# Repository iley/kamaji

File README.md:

# Kamaji quiz game system

See [kamaji.cc](http://kamaji.cc) for assembly instructions and additional information.

Directories:

* `firmware`: main source code;
* `demo`: code samples;
* `3d`: [OpenSCAD](http://www.openscad.org/) models for the enclosure;
* `pcb`: schematic and printed circuit board layout in [KiCAD](http://kicad-pcb.org/) format;
* `misc`: the rest.

## SDK

We use [PlatformIO](http://platformio.org) with
[Arduino](http://platformio.org/frameworks/arduino) framework. It should also
be possible to compile the code with the official Arduino IDE.

## Compile and flash firmware

For v1 and v3 custom fuses must be programmed before first flashing.

```
pio run -e v1 -t fuses
```

Select the correct board version (v1, v2, v3) and flash it with:

```
pio run -e v1 -t upload
```

## Hardware

**The recommended version for new builds is "Classic V1".**

* V1 uses an ATmega328p running at 8MHz without an external oscillator. [USBasp](http://www.fischl.de/usbasp/) can be used for programming.
* V2 uses ATmega32u4 and a 128x64 graphics screen.
* V3 runs on ATmega328p with a 16MHz oscillator and and utilizes a PCF8574 I/O extender chip.
* "Classic V1" is an updated revision of V1. Fully compatible from software point of view.
* "Headless" is a USB MIDI device without a screen or buttons. Built around "Pro Micro" boards (ATMega32U4).

## Code style

Let's stick to [Google C++ Style Guide](https://google.github.io/styleguide/cppguide.html).

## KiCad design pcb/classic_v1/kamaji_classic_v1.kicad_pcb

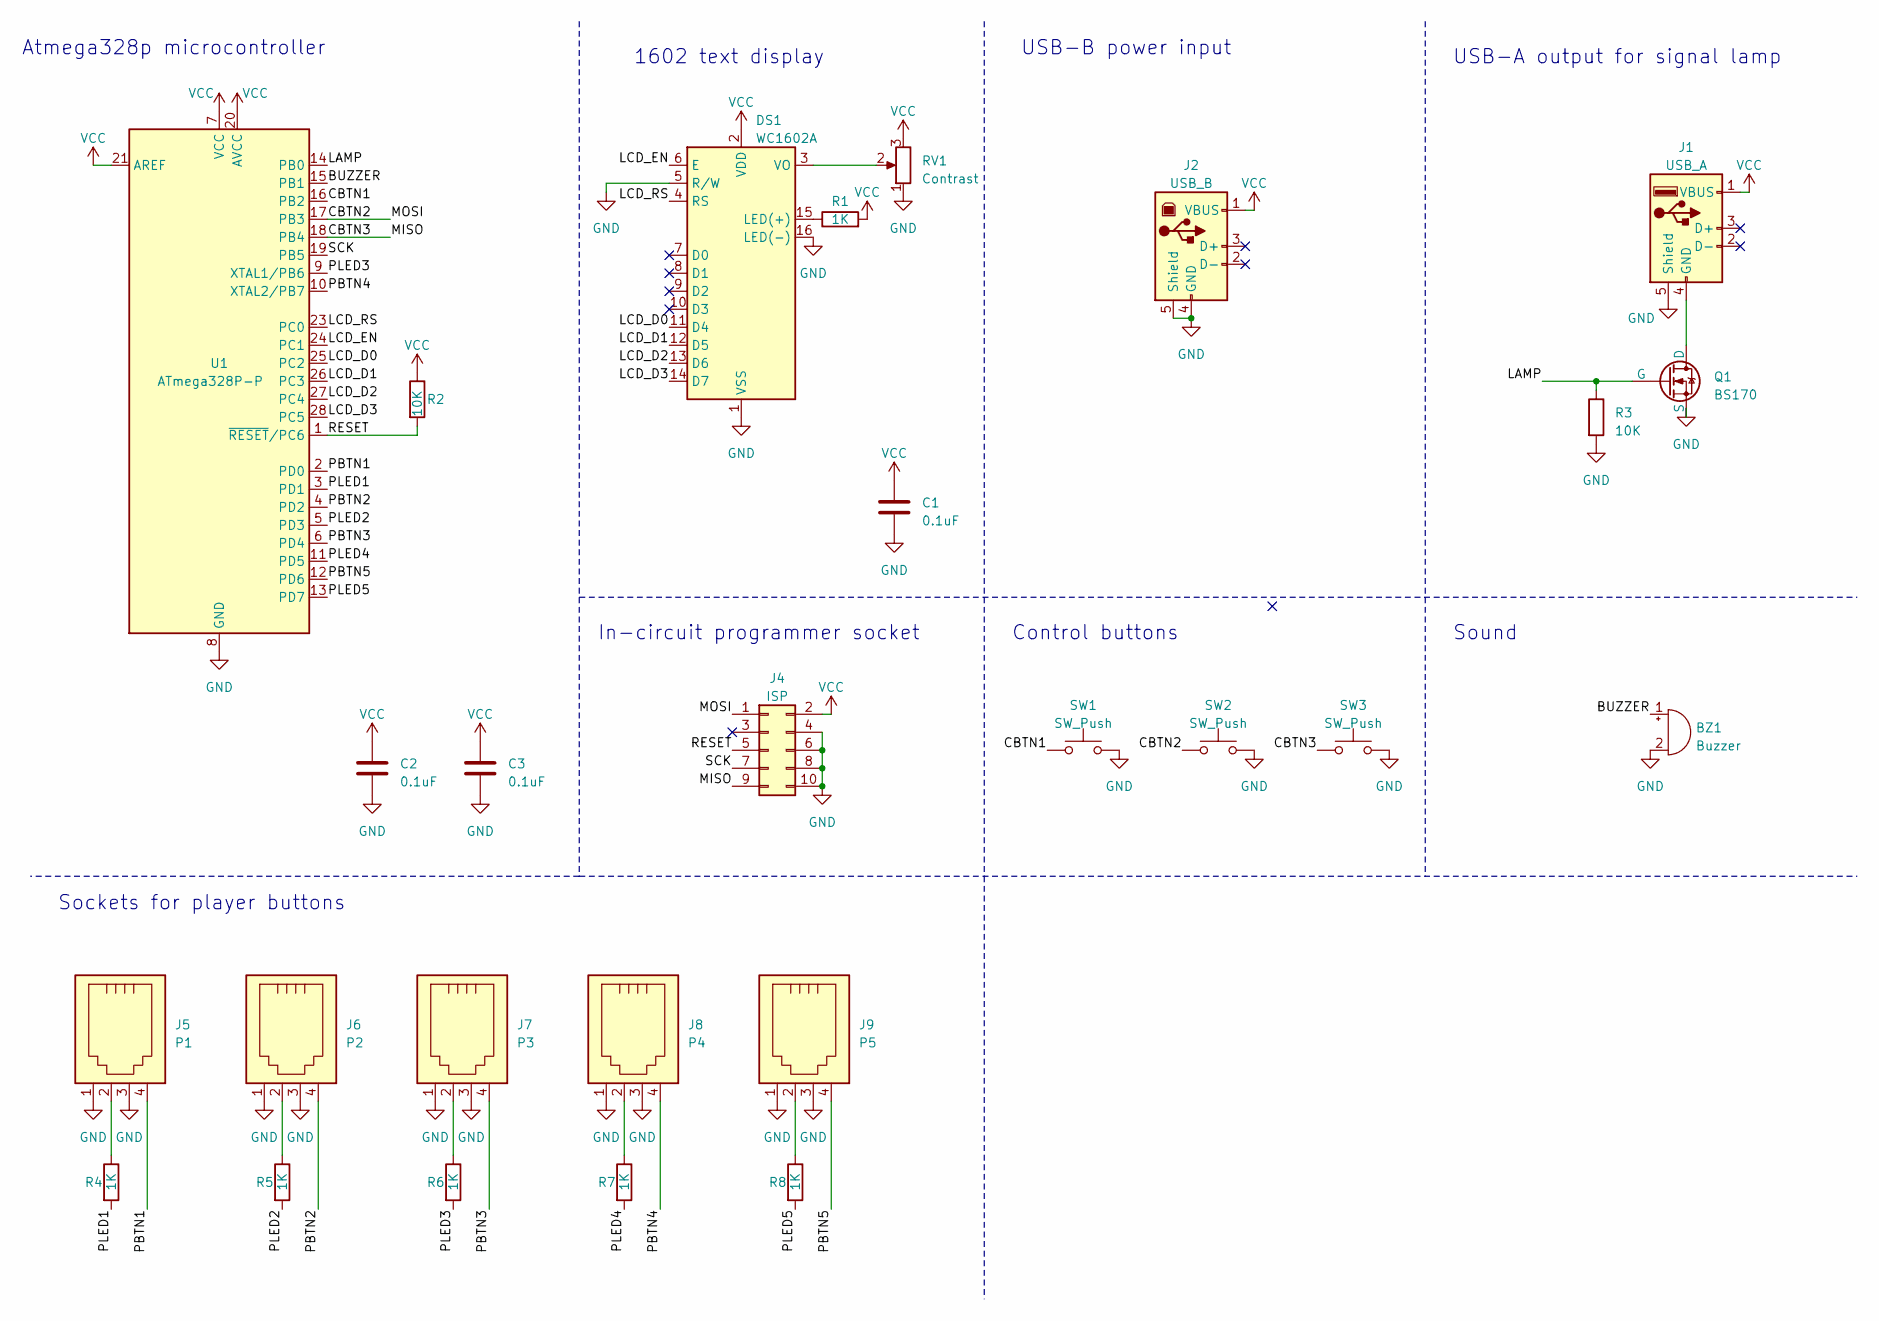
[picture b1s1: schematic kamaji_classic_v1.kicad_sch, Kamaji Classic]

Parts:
BZ1: Buzzer; Buzzer_12x9.5RM7.6
C1, C2, C3: 0.1uF; C_Disc_D3.8mm_W2.6mm_P2.50mm
DS1: WC1602A
J1: USB_A; USB_A_Connfly_DS1095
J2: USB_B; USB_B_Lumberg_2411_02_Horizontal
J4: ISP; IDC-Header_2x05_P2.54mm_Horizontal
J5: P1; RJ10
J6: P2; RJ10
J7: P3; RJ10
J8: P4; RJ10
J9: P5; RJ10
Q1: BS170; TO-92_HandSolder
R1, R4, R5, R6, R7, R8: 1K; R_Axial_DIN0207_L6.3mm_D2.5mm_P10.16mm_Horizontal
R2, R3: 10K; R_Axial_DIN0207_L6.3mm_D2.5mm_P10.16mm_Horizontal
RV1: Contrast; Potentiometer_Vishay_T73YP_Vertical
SW1, SW2, SW3: SW_Push; SW_PUSH-12mm
U1: ATmega328P-P; DIP-28_W7.62mm

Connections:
/BUZZER: BZ1.1 (-), U1.15 (PB1)
/CBTN1: SW1.1, U1.16 (PB2)
/CBTN2: J4.1, SW2.1, U1.17 (PB3)
/CBTN3: J4.9, SW3.1, U1.18 (PB4)
/LAMP: Q1.2 (G), R3.1, U1.14 (PB0)
/LCD_D0: DS1.11 (D4), U1.25 (PC2)
/LCD_D1: DS1.12 (D5), U1.26 (PC3)
/LCD_D2: DS1.13 (D6), U1.27 (PC4)
/LCD_D3: DS1.14 (D7), U1.28 (PC5)
/LCD_EN: DS1.6 (E), U1.24 (PC1)
/LCD_RS: DS1.4 (RS), U1.23 (PC0)
/PBTN1: J5.4, U1.2 (PD0)
/PBTN2: J6.4, U1.4 (PD2)
/PBTN3: J7.4, U1.6 (PD4)
/PBTN4: J8.4, U1.10 (XTAL2/PB7)
/PBTN5: J9.4, U1.12 (PD6)
/PLED1: R4.2, U1.3 (PD1)
/PLED2: R5.2, U1.5 (PD3)
/PLED3: R6.2, U1.9 (XTAL1/PB6)
/PLED4: R7.2, U1.11 (PD5)
/PLED5: R8.2, U1.13 (PD7)
/RESET: J4.5, R2.2, U1.1 (~RESET/PC6)
/SCK: J4.7, U1.19 (PB5)
GND: BZ1.2 (+), C1.2, C2.2, C3.2, DS1.1 (VSS), DS1.5 (R/W), DS1.16 (LED(-)), J1.5 (Shield), J2.4 (GND), J2.5 (Shield), J4.4, J4.6, J4.8, J4.10, J5.1, J5.3, J6.1, J6.3, J7.1, J7.3, J8.1, J8.3, J9.1, J9.3, Q1.3 (S), R3.2, RV1.1, SW1.2, SW2.2, SW3.2, U1.8 (GND), U1.22 (GND)
unnamed: DS1.15 (LED(+)), R1.1
unnamed: DS1.3 (VO), RV1.2
unnamed: J1.4 (GND), Q1.1 (D)
unnamed: J5.2, R4.1
unnamed: J6.2, R5.1
unnamed: J7.2, R6.1
unnamed: J8.2, R7.1
unnamed: J9.2, R8.1
VCC: C1.1, C2.1, C3.1, DS1.2 (VDD), J1.1 (VBUS), J2.1 (VBUS), J4.2, R1.2, R2.1, RV1.3, U1.7 (VCC), U1.20 (AVCC), U1.21 (AREF)

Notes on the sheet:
1602 text display
Atmega328p microcontroller
USB-B power input
Sockets for player buttons
Sound
Control buttons
USB-A output for signal lamp
In-circuit programmer socket

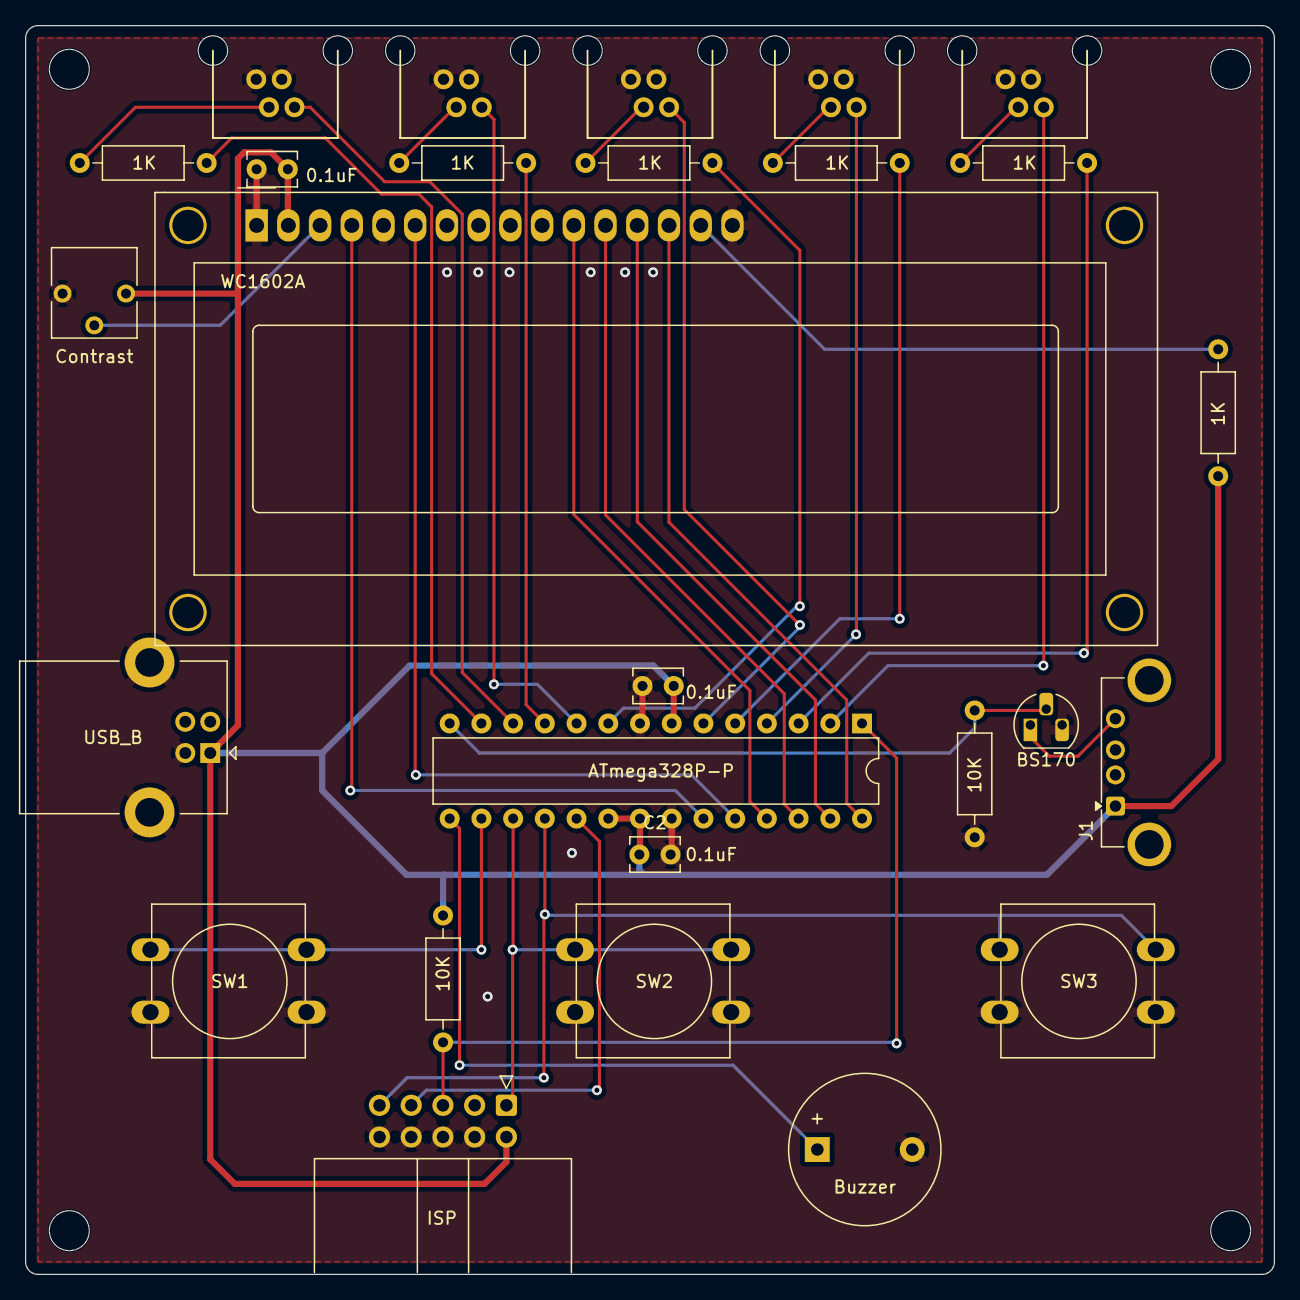
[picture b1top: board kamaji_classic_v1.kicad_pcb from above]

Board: 2 copper layers, 100.0 x 100.0 mm, 27 parts (0 on the bottom side), 33 nets.

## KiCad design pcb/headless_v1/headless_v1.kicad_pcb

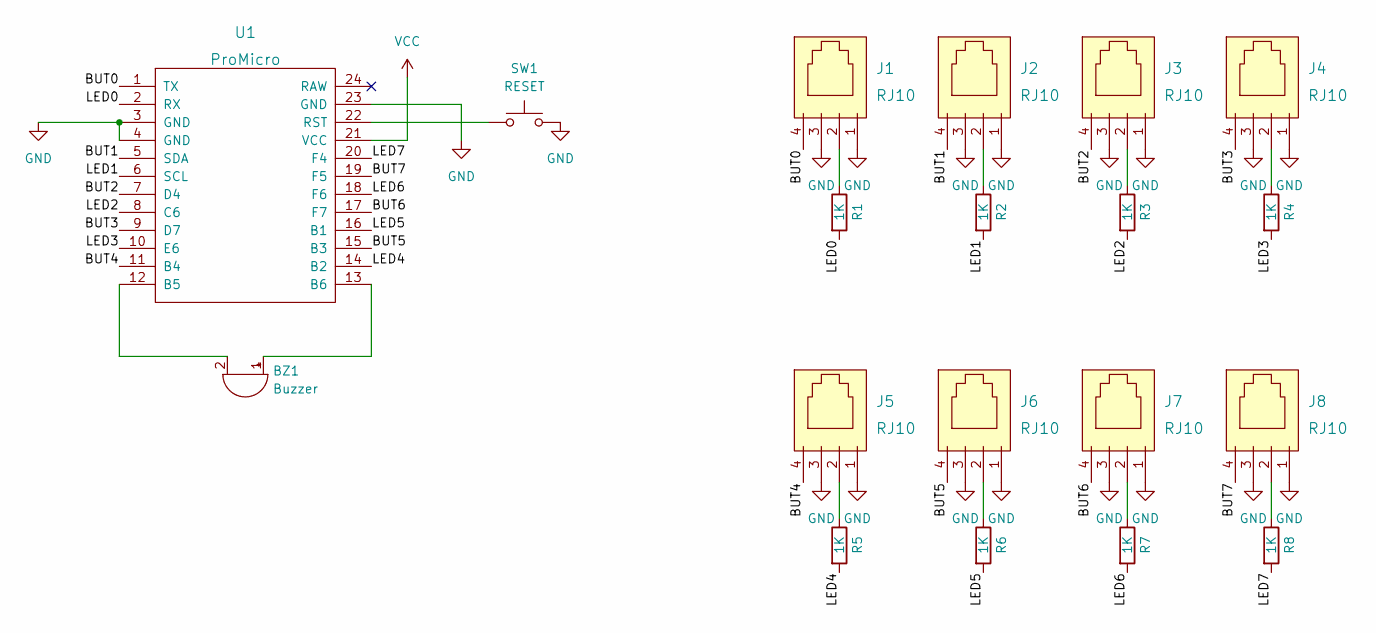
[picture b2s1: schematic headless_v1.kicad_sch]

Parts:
BZ1: Buzzer; Buzzer_12x9.5RM7.6
J1, J2, J3, J4, J5, J6, J7, J8: RJ10
R1, R2, R3, R4, R5, R6, R7, R8: 1K; R_Axial_DIN0207_L6.3mm_D2.5mm_P10.16mm_Horizontal
SW1: RESET; SW_PUSH_6mm
U1: ProMicro

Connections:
/BUT0: J1.4, U1.1 (TX)
/BUT1: J2.4, U1.5 (SDA)
/BUT2: J3.4, U1.7 (D4)
/BUT3: J4.4, U1.9 (D7)
/BUT4: J5.4, U1.11 (B4)
/BUT5: J6.4, U1.15 (B3)
/BUT6: J7.4, U1.17 (F7)
/BUT7: J8.4, U1.19 (F5)
/LED0: R1.2, U1.2 (RX)
/LED1: R2.2, U1.6 (SCL)
/LED2: R3.2, U1.8 (C6)
/LED3: R4.2, U1.10 (E6)
/LED4: R5.2, U1.14 (B2)
/LED5: R6.2, U1.16 (B1)
/LED6: R7.2, U1.18 (F6)
/LED7: R8.2, U1.20 (F4)
GND: J1.1, J1.3, J2.1, J2.3, J3.1, J3.3, J4.1, J4.3, J5.1, J5.3, J6.1, J6.3, J7.1, J7.3, J8.1, J8.3, SW1.2, U1.3 (GND), U1.4 (GND), U1.23 (GND)
unnamed: BZ1.1 (-), U1.13 (B6)
unnamed: BZ1.2 (+), U1.12 (B5)
unnamed: J1.2, R1.1
unnamed: J2.2, R2.1
unnamed: J3.2, R3.1
unnamed: J4.2, R4.1
unnamed: J5.2, R5.1
unnamed: J6.2, R6.1
unnamed: J7.2, R7.1
unnamed: J8.2, R8.1
unnamed: SW1.1, U1.22 (RST)
VCC: U1.21 (VCC)

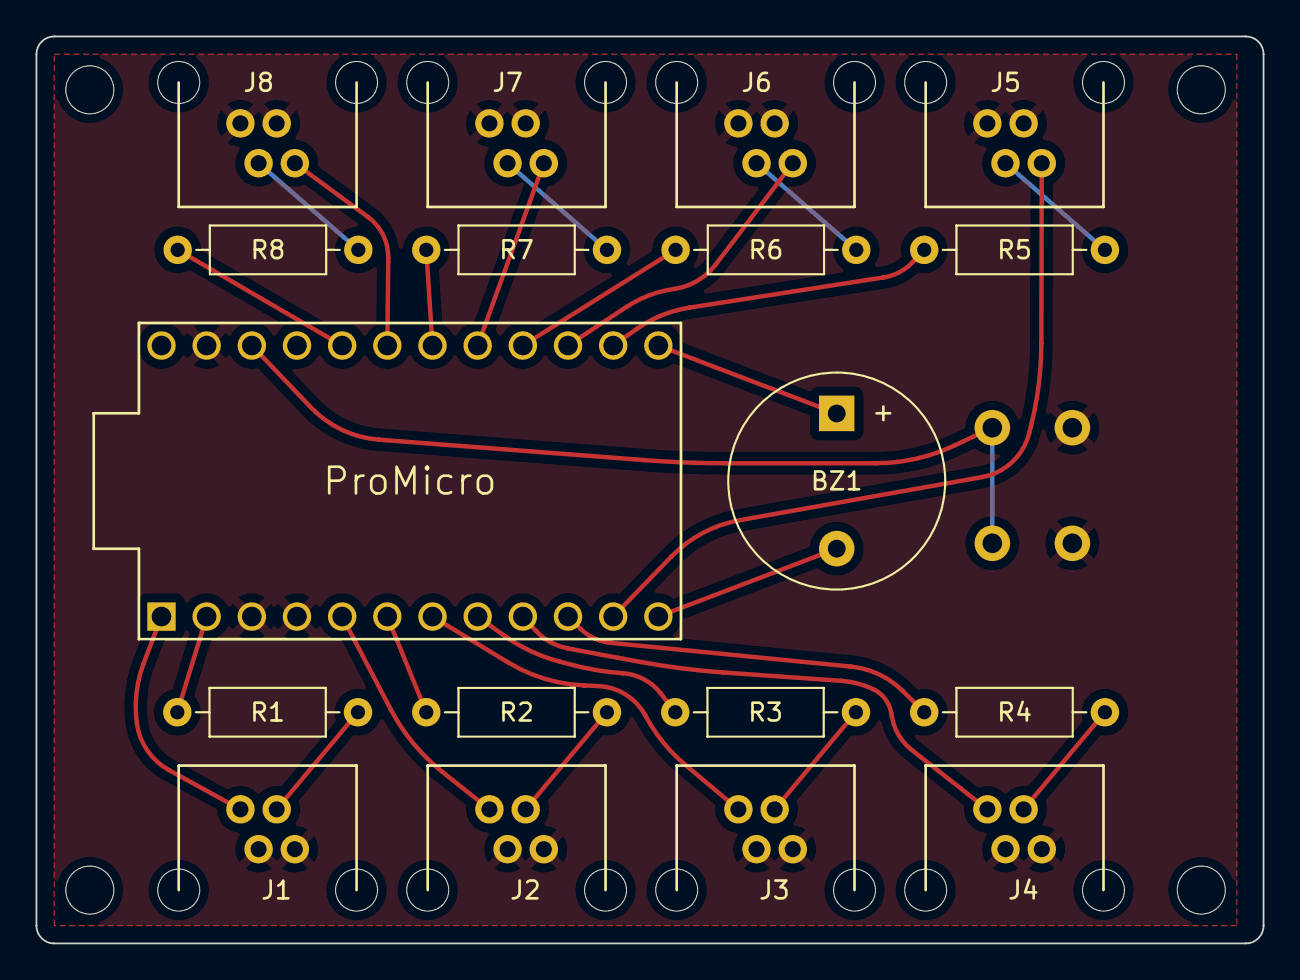
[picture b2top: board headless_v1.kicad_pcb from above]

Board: 2 copper layers, 69.0 x 51.0 mm, 19 parts (1 on the bottom side), 28 nets.

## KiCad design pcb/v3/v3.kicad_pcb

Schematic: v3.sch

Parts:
C1, C4, C5, C7: 0.1uF; C_1206_3216Metric_Pad1.42x1.75mm_HandSolder
C2, C3: 20pF; C_1206_3216Metric_Pad1.42x1.75mm_HandSolder
C6: 20uF; C_1206_3216Metric_Pad1.42x1.75mm_HandSolder
C8: 10uF; C_1206_3216Metric_Pad1.42x1.75mm_HandSolder
J1, J3, J4, J5, J6, J7: RJ10
J2: ICSP; IDC-Header_2x05_P2.54mm_Horizontal
J8: BOOST; DD1718PA
J9: USB_B
J10: USB_A
JP1: SND24V; PinHeader_1x02_P2.54mm_Vertical
JP2: SND5V; PinHeader_1x02_P2.54mm_Vertical
LS1: Speaker; Buzzer_ARIO_98dB
Q2: 2N3904; TO-92_Inline_Wide
Q3: BS170; TO-92_Inline_Wide
R1, R2, R3, R5, R8, R9, R10, R12, R18: 1K; R_1206_3216Metric_Pad1.42x1.75mm_HandSolder
R4, R19: 10K; R_1206_3216Metric_Pad1.42x1.75mm_HandSolder
R6, R7: 4K7; R_1206_3216Metric_Pad1.42x1.75mm_HandSolder
RV1: CONTRAST; Potentiometer_Vishay_T73YP_Vertical
RV2: VOLUME; Potentiometer_Wheel_16mm
SW1: CTL1; Pushbutton_12mm
SW2: CTL2; Pushbutton_12mm
SW3: CTL3; Pushbutton_12mm
U1: ATmega328P-PU; DIP-28_W7.62mm
U2: PCF8574; DIP-16_W7.62mm_LongPads
U3: RC1602A; LCD2004
Y1: 16MHz; Crystal_HC49-U_Vertical

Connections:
+24V: C6.1, J8.3, JP1.2
/CBTN1: J2.1, SW1.1, U1.17 (PB3)
/CBTN2: J2.7, SW2.1, U1.19 (PB5)
/CBTN3: J2.9, SW3.1, U1.18 (PB4)
/LAMP: R18.2, U1.14 (PB0)
/LCD0: U1.23 (PC0), U3.11 (DB4)
/LCD1: U1.24 (PC1), U3.12 (DB5)
/LCD2: U1.25 (PC2), U3.13 (DB6)
/LCD3: U1.26 (PC3), U3.14 (DB7)
/LCDE: U1.12 (PD6), U3.6 (E)
/LCDRS: U1.13 (PD7), U3.4 (RS)
/PBTN1: J1.4, U1.11 (PD5)
/PBTN2: J3.4, U1.6 (PD4)
/PBTN3: J4.4, U1.5 (PD3)
/PBTN4: J5.4, U1.4 (PD2)
/PBTN5: J6.4, U1.3 (PD1)
/PBTN6: J7.4, U1.2 (PD0)
/PLED1: R1.2, U2.4 (P0)
/PLED2: R2.2, U2.5 (P1)
/PLED3: R3.2, U2.6 (P2)
/PLED4: R5.2, U2.7 (P3)
/PLED5: R8.2, U2.9 (P4)
/PLED6: R9.2, U2.10 (P5)
/RST: J2.5, R4.2, U1.1 (~RESET~/PC6)
/SCL: R7.2, U1.28 (PC5), U2.14 (SCL)
/SDA: R6.2, U1.27 (PC4), U2.15 (SDA)
/SPK: R12.1, U1.15 (PB1)
/XTAL1: C2.2, U1.9 (XTAL1/PB6), Y1.1
/XTAL2: C3.2, U1.10 (XTAL2/PB7), Y1.2
GND: C1.2, C2.1, C3.1, C4.2, C5.2, C6.2, C7.2, C8.1, J1.1, J1.3, J2.4, J2.6, J2.8, J2.10, J3.1, J3.3, J4.1, J4.3, J5.1, J5.3, J6.1, J6.3, J7.1, J7.3, J8.2, J8.4, J9.4 (GND), J9.5 (Shield), J10.5 (Shield), Q2.1 (E), Q3.3, R19.2, RV1.1, RV2.1, SW1.2, SW2.2, SW3.2, U1.8 (GND), U1.22 (GND), U2.1 (A0), U2.2 (A1), U2.3 (A2), U2.8 (VSS), U3.1 (VSS), U3.5 (R/W), U3.7 (DB0), U3.8 (DB1), U3.9 (DB2), U3.10 (DB3), U3.16 (K)
unnamed: C8.2, LS1.1, Q2.3 (C)
unnamed: J1.2, R1.1
unnamed: J3.2, R2.1
unnamed: J4.2, R3.1
unnamed: J5.2, R5.1
unnamed: J6.2, R8.1
unnamed: J7.2, R9.1
unnamed: J10.4 (GND), Q3.1
unnamed: JP1.1, JP2.2, RV2.3
unnamed: LS1.2, RV2.2
unnamed: Q2.2 (B), R12.2
unnamed: Q3.2, R18.1, R19.1
unnamed: R10.1, U3.15 (A/VEE)
unnamed: RV1.2, U3.3 (VO)
VCC: C1.1, C4.1, C5.1, C7.1, J2.2, J8.5, J9.1 (VBUS), J10.1 (VBUS), JP2.1, R4.1, R6.1, R7.1, R10.2, RV1.3, U1.7 (VCC), U1.20 (AVCC), U1.21 (AREF), U2.16 (VDD), U3.2 (VDD)

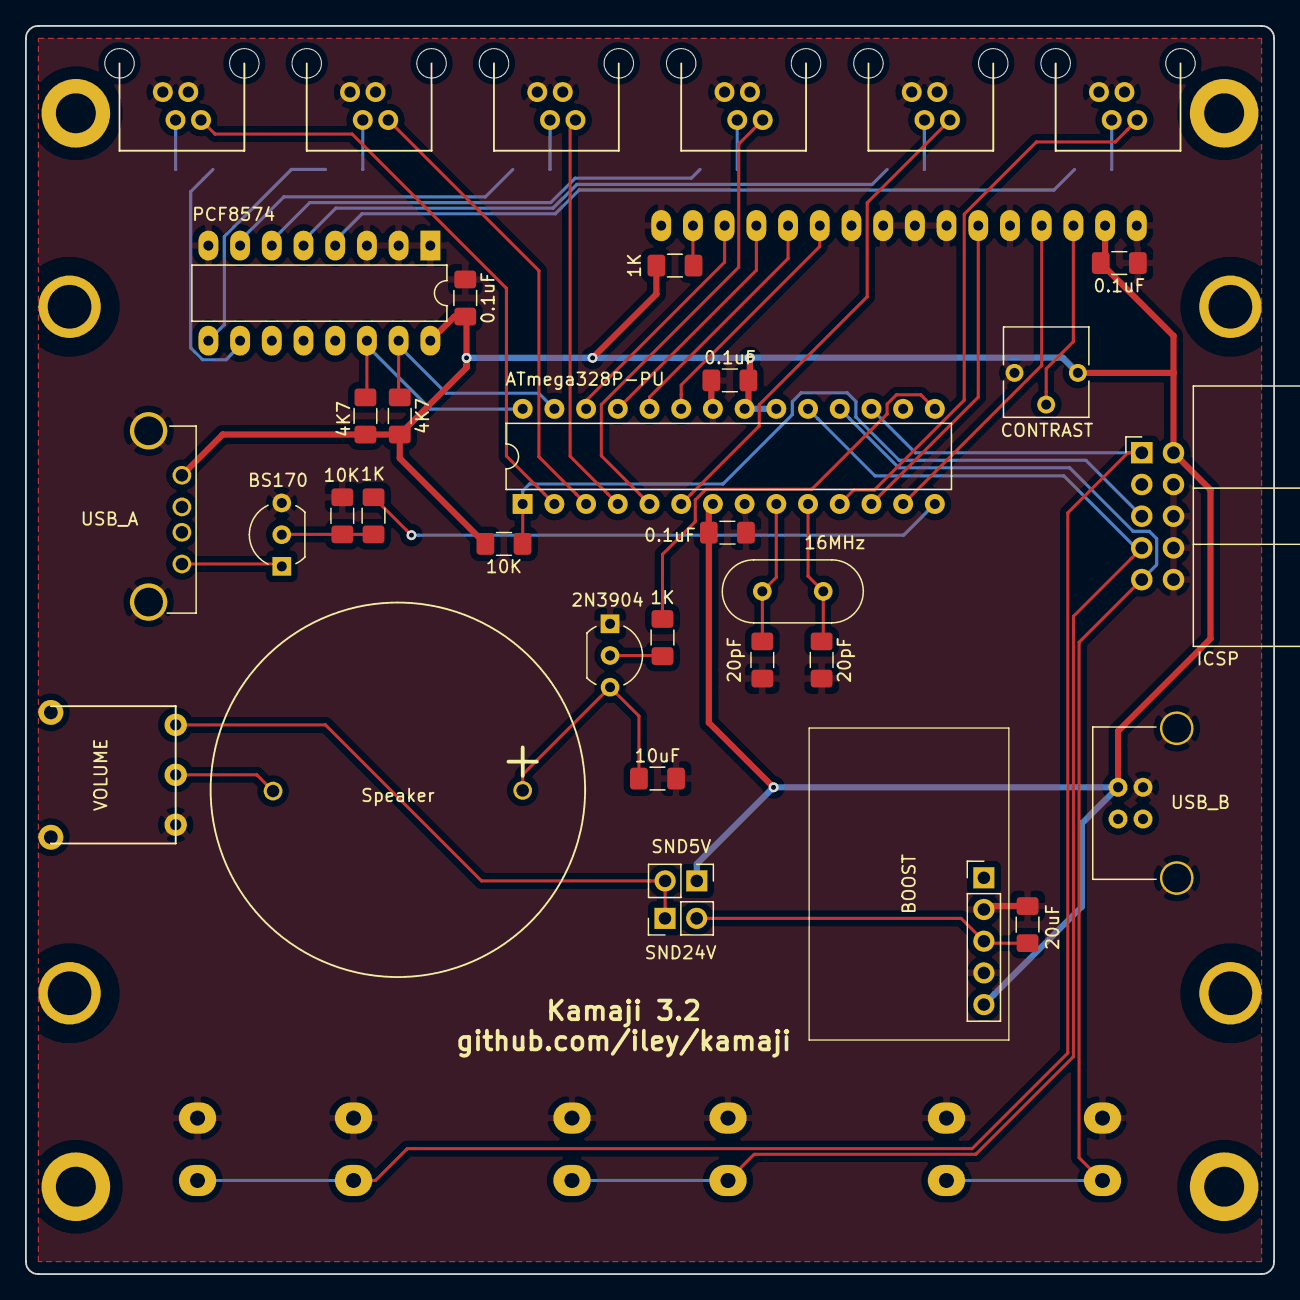
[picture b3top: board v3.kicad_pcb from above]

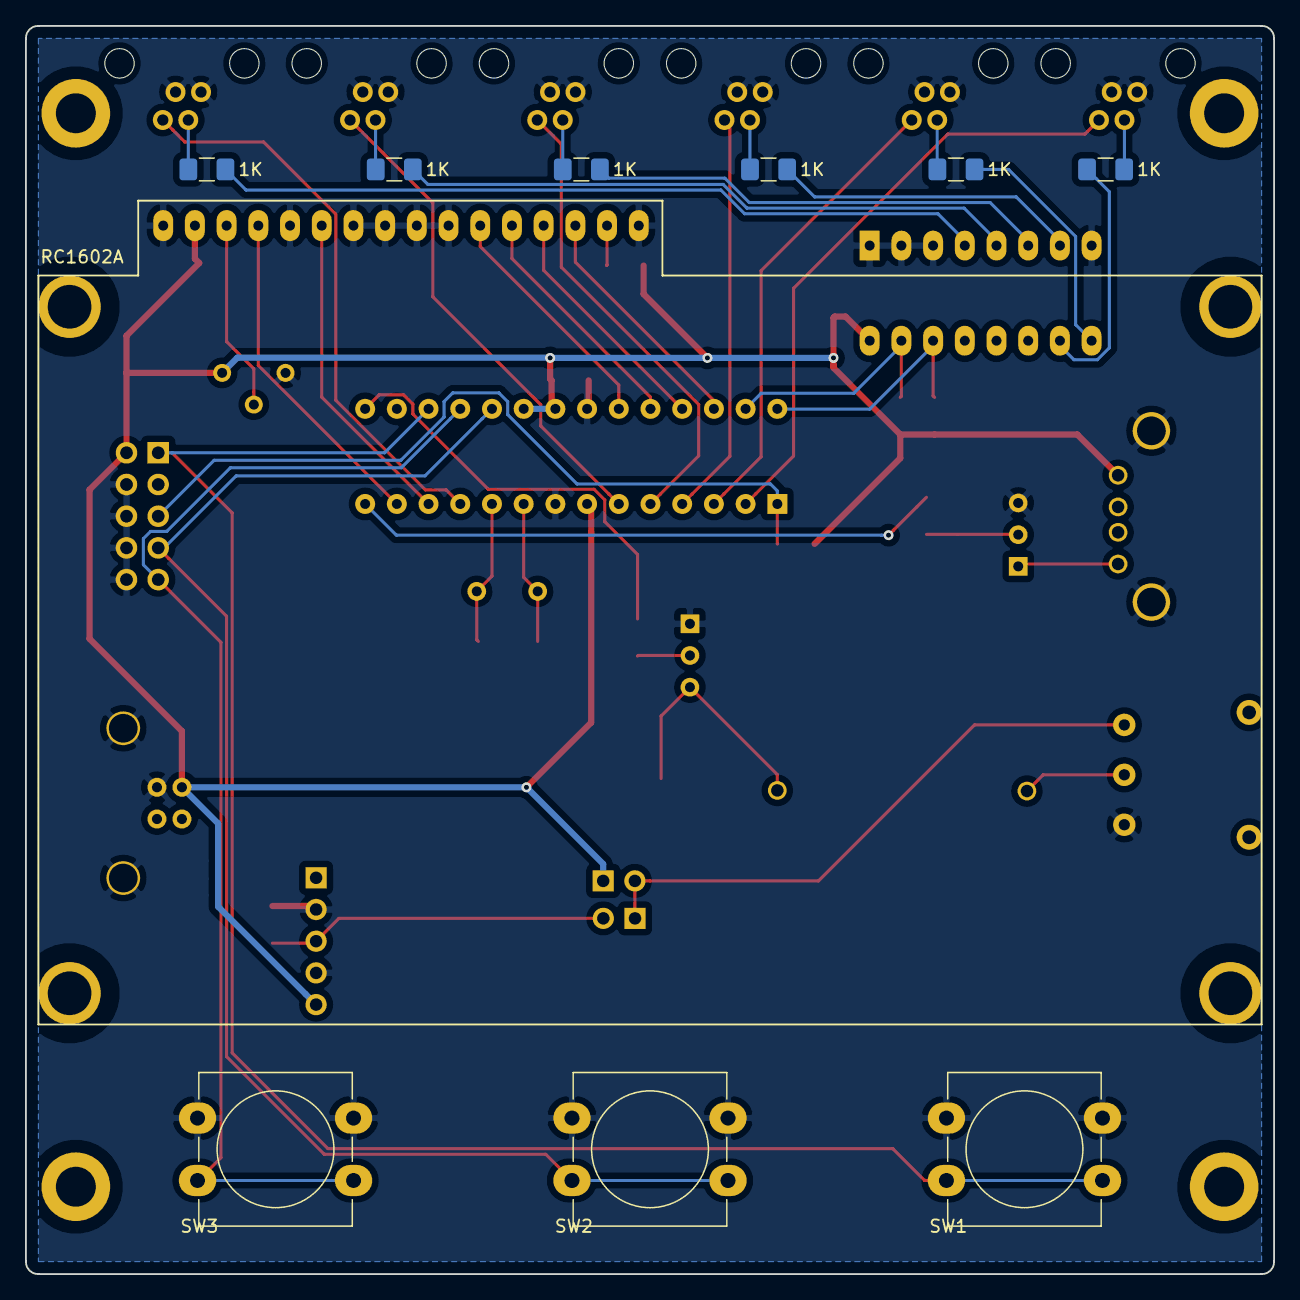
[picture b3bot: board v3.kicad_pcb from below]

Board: 2 copper layers, 100.0 x 100.0 mm, 45 parts (10 on the bottom side), 45 nets.

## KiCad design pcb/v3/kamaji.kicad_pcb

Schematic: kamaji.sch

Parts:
C1, C2, C5: 0.1uF; C_Disc_D3.8mm_W2.6mm_P2.50mm
C3, C4: 22pF; C_Disc_D3.8mm_W2.6mm_P2.50mm
DS1: WC1602A; LCD2004
F1: 1A; C_Disc_D5.0mm_W2.5mm_P5.00mm
J1: UART_6pin; Pin_Header_Angled_1x06_Pitch2.54mm
J2: ICSP; Pin_Header_Straight_2x05_Pitch2.54mm
J3, J4, J5, J6, J7, J8: RJ10
J9: USB_B
J10: USB_A
JP1: 5V; Pin_Header_Straight_1x02_Pitch2.54mm
JP2: 24V; Pin_Header_Straight_1x02_Pitch2.54mm
JP3: UART_PWR; Pin_Header_Straight_1x02_Pitch2.54mm
LS1: 98dB; Buzzer_ARIO_98dB
Q1: 2N3904; TO-92_Inline_Narrow_Oval
Q2: IRL540N; TO-220-3_Horizontal
R1: 10K; R_Axial_DIN0207_L6.3mm_D2.5mm_P10.16mm_Horizontal
R2, R3, R4, R5, R6, R7, R8: 220R; R_Axial_DIN0207_L6.3mm_D2.5mm_P10.16mm_Horizontal
R9: 1K; R_Axial_DIN0207_L6.3mm_D2.5mm_P10.16mm_Horizontal
R10: R; R_Axial_DIN0207_L6.3mm_D2.5mm_P10.16mm_Horizontal
RV1: POT; Potentiometer_Wheel_16mm
RV2: POT; Potentiometer_Triwood_RM-065
SW1, SW2, SW3: SW_Push; Pushbutton_12mm
U1: ATMEGA644P-20PU; DIP-40_W15.24mm_LongPads
U2: BOOST_24V; Pin_Header_Straight_1x05_Pitch2.54mm
Y1: 20MHz; Crystal_HC49-U_Vertical

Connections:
/AVR_RX: J1.4, U1.14
/AVR_TX: J1.5, U1.15
/BTN1: J3.4, U1.19
/BTN2: J4.4, U1.22
/BTN3: J5.4, U1.26
/BTN4: J6.4, U1.35
/BTN5: J7.4, U1.37
/BTN6: J8.4, U1.39
/CBTN1: SW1.1, U1.3
/CBTN2: SW2.1, U1.2
/CBTN3: SW3.1, U1.1
/LAMP: Q2.1 (G), R10.1, U1.40
/LCD_D4: DS1.11, U1.27
/LCD_D5: DS1.12, U1.28
/LCD_D6: DS1.13, U1.29
/LCD_D7: DS1.14, U1.33
/LCD_EN: DS1.6, U1.24
/LCD_RS: DS1.4, U1.23
/LED1: R2.2, U1.20
/LED2: R5.2, U1.21
/LED3: R3.2, U1.25
/LED4: R4.2, U1.34
/LED5: R6.2, U1.36
/LED6: R7.2, U1.38
/MISO: J2.9, U1.7
/MOSI: J2.1, U1.6
/RESET: J2.5, R1.2, U1.9
/SCK: J2.7, U1.8
/SOUND: R9.2, U1.4
GND: C1.2, C2.2, C3.1, C4.2, C5.2, DS1.1, DS1.5, DS1.7, DS1.8, DS1.9, DS1.10, DS1.16, J1.1, J2.4, J2.6, J2.8, J2.10, J3.1, J3.3, J4.1, J4.3, J5.1, J5.3, J6.1, J6.3, J7.1, J7.3, J8.1, J8.3, J9.4 (GND), J9.5 (Shield), J10.5 (Shield), Q1.1, Q2.3 (S), R10.2, RV1.1, RV2.1, SW1.2, SW2.2, SW3.2, U1.11, U1.31, U1.32, U2.2, U2.4
unnamed: C3.2, U1.12, Y1.1
unnamed: C4.1, U1.13, Y1.2
unnamed: DS1.3, RV2.2
unnamed: DS1.15, R8.2
unnamed: F1.2, J9.1 (VBUS)
unnamed: J1.3, JP3.1
unnamed: J3.2, R2.1
unnamed: J4.2, R5.1
unnamed: J5.2, R3.1
unnamed: J6.2, R4.1
unnamed: J7.2, R6.1
unnamed: J8.2, R7.1
unnamed: J10.4 (GND), Q2.2 (D)
unnamed: JP1.2, JP2.2, RV1.3
unnamed: JP2.1, U2.3
unnamed: LS1.1, RV1.2
unnamed: LS1.2, Q1.3
unnamed: Q1.2, R9.1
VCC: C1.1, C2.1, C5.1, DS1.2, F1.1, J2.2, J10.1 (VBUS), JP1.1, JP3.2, R1.1, R8.1, RV2.3, U1.10, U1.30, U2.5

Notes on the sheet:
POWER
LAMP
CONTROL BUTTONS
SOUND
TODO: Replace boost converter footprint
UART CONNECTOR
LCD SCREEN

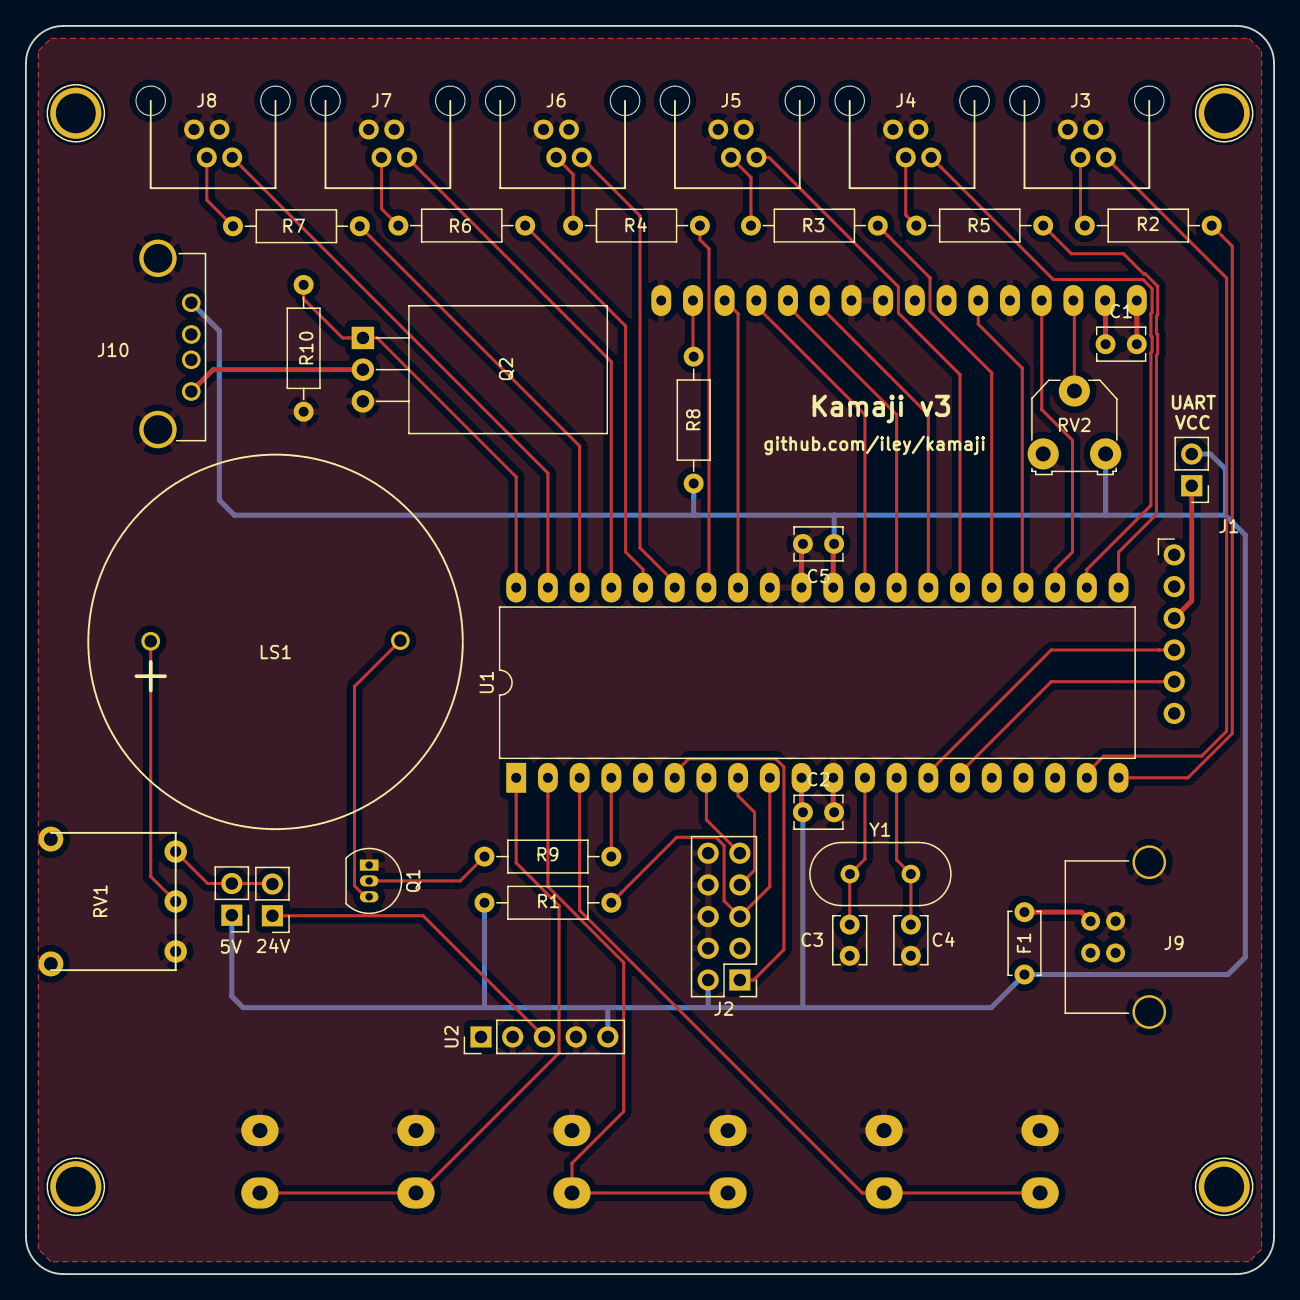
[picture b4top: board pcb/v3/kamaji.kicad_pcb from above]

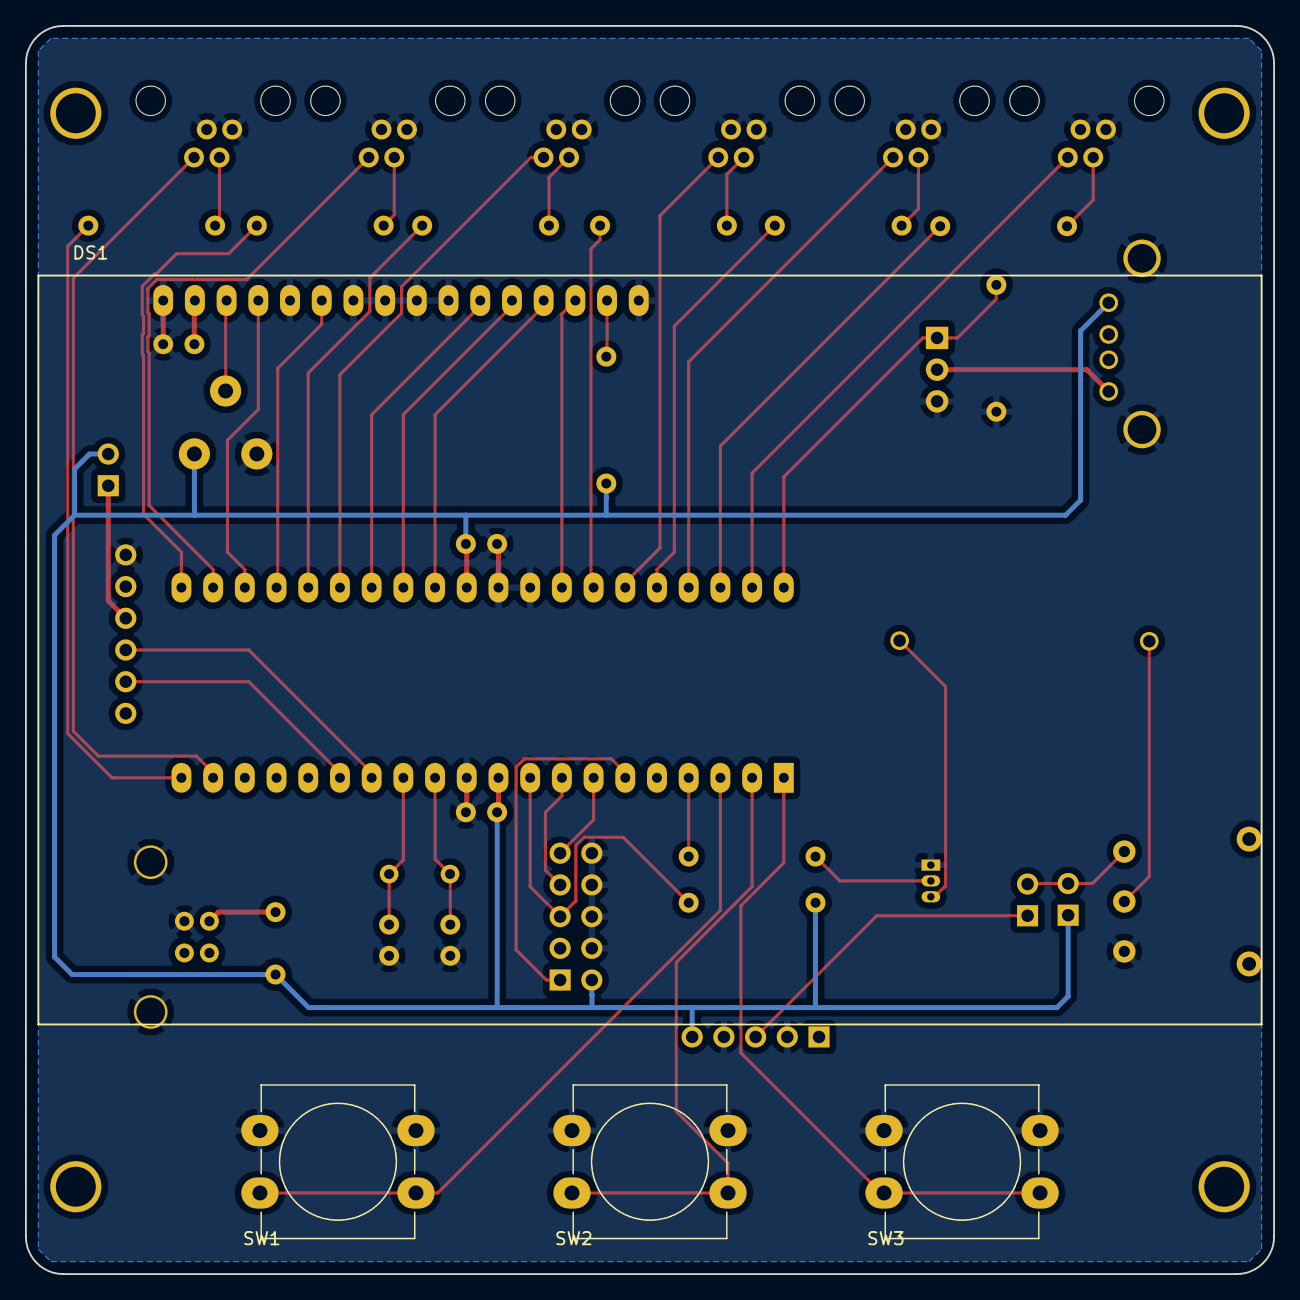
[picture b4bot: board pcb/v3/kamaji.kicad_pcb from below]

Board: 2 copper layers, 100.0 x 100.0 mm, 41 parts (4 on the bottom side), 49 nets.

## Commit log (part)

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2017-07-15 Initial scad models
2017-07-16 create pcb directory
2017-07-16 start the pcb layout
2017-07-16 some progress on the schematics
2017-07-16 first version of the schematic
2017-07-17 get rid of the shift register
2017-07-17 rename design to misc, update readme
2017-07-17 fix markdown formatting in readme
2017-07-19 add current-limiting resistors for player LEDs
2017-07-20 minor changes to the schematic
2017-07-20 change component placement for easier routing
2017-07-20 a few more component moves
2017-07-20 define net classes
2017-07-20 start drawing traces
2017-07-21 a few minor changes to the PCB layout
2017-07-21 re-route a resistor
2017-07-21 re-route a potentiometer
2017-07-21 center the player sockets
2017-07-21 add mounting holes
2017-07-21 move a few tracks
2017-07-21 move another resistor
2017-07-22 change mounting hole sizes, move labels around
2017-07-22 final touches to the PCB design
2017-07-22 replace TIP120 with a MOSFET, drive the speaker directly
2017-07-22 fix mounting holes
2017-07-22 use a polarized capacitor for the speaker
2017-07-22 fix the capacitor labels
2017-07-22 switch to a 10-pin ICSP connector
2017-07-22 generate gerbers
2017-07-23 move usb sockets
2017-07-23 move player sockets
2017-07-23 change a capacitor value
2017-07-25 PCB: final touches
2017-07-27 Fixes
2017-07-27 Tweaks
2017-07-29 remove the extra trace going to one of the buttons
2017-07-30 start laying out a new, smaller PCB
2017-07-30 lay out the 1.1 PCB
2017-07-30 move the speaker footprint
2017-08-01 rename pcb to pcb1.1 to make the 1.0 version available at master
2017-08-07 pcb v1.1: re-route crystal, a few other adjustments
2017-08-07 move the crystal and a usb socket
2017-08-09 platformio configuration for the hardware
2017-08-09 rename "v1" to "firmware"
    it's going to contain sources for multiple hardware revisions
2017-08-09 fix formatting, remove an old TODO
2017-08-11 configure pins for v1, remove serial
2017-08-11 implement xDigitalRead and xDigitalWrite
2017-08-11 implement xPinMode
2017-08-11 use xPinMode/xDigitalRead/xDigitalWrite
2017-08-11 start using PB6 and PB7
2017-08-11 fix a typo in xPinMode
2017-08-11 add a script for setting correct FUSE values
2017-08-12 sketch an LCD support 3D model
2017-08-14 set LCD support dimensions
2017-08-14 Bottom model with low fence
2017-08-14 Adjusted bottom
2017-08-14 minor adjustments to bottom.scad
2017-08-16 Add top model
2017-08-17 Correct measures
2017-08-17 enclosure top: minor adjustments
2017-08-18 Fix for 2 mm
2017-08-18 declare lamp pin
2017-08-18 update the sound demo for v1
2017-08-18 dimensions of the top enclosure
2017-08-18 button cap model
2017-08-18 add todo
2017-08-22 rename files in 3d/
2017-08-22 remove old 3d model
2017-08-22 lamp support
2017-08-22 get rid of compilation warnings
2017-08-23 adjust the buttons diameter
2017-08-23 Revert "adjust buttons diameter again"
    This reverts commit 4d08f24b96e21f3ca8a92ca791474b8490ea357c.
2017-08-23 change tones
2017-08-23 update the sound demo
2017-08-23 move stuff around
2017-08-23 start the 2.0 PCB design
2017-08-23 declarations for the developer mode
2017-08-23 use anonymous namespaces for module-local variables
2017-08-23 save some memory by reusing the same buffer for captions
2017-08-23 use #if instead of #ifdef
2017-08-23 remove a duplicate constant
2017-08-23 initialize resetStarted
2017-08-23 reverse the player socket order on v1
2017-08-30 enclosure: minor adjustments
2017-08-31 try fixing the cutout sizes
2017-09-01 change the lcd support height
2017-09-01 fix lamp behaviour
2017-09-06 fix the top yet again
2017-09-07 Various changes
2017-09-07 Fixing compilation
2017-09-07 Revert "change buttons height"
    This reverts commit 451372d9556a0305292e385cb7759c9dfeb46305.
2017-09-07 fix the buttons height
2017-09-08 buttons
2017-09-08 stuff
2017-09-09 Delay for brain
2017-09-09 Delay for brain fix
2017-09-12 Box with a board
2017-09-12 Board for top
2017-09-12 brain: play sound after the random delay
2017-09-13 set v1 as the default environment for platformio
2017-09-13 fix a format string
2017-09-13 Fix top board
2017-09-13 bolt heads on the top
2017-09-13 bigger button holes
2017-09-16 Scores
2017-09-17 Use more verbose flags
2017-10-02 add v1 configuration with 4 players
2017-10-02 get rid of compiler warnings
2017-10-02 a few connections on the 2.0 PCB schematic
2017-10-03 PCB 1.0 wiring
2017-10-09 add LICENSE.txt
2017-10-09 pull reset up since it's active-low
2017-10-09 add jumper on power, comments
2017-10-10 update title on 1.0 schematic
2017-10-11 lcd demo: print character table
2017-10-12 add a daughter board connector
2017-10-17 start the 2.0 schematic from scratch
2017-10-21 psb: add screen, sound, usb, dummy load and ICSP
2017-10-21 pcb: add the rest of the components to the schematic
2017-10-21 pcb: minor adjustments
2017-10-22 fix a typo
2017-10-22 use 4 parallel resistors for the dummy load
2017-10-22 start mapping symbols to footprints
2017-11-01 move kicad libs to a separate directory
2017-11-01 use a graphic display instead of 2004
2017-11-18 pcb: delete the sound circuit
2017-11-25 minor pcb changes
2017-11-28 Countdown
2017-12-04 try building with CircleCI
2017-12-04 build for all environments
2017-12-04 add CircleCI badge to the readme
2017-12-04 build all environments at once
2017-12-08 sound and menu tweaks
2017-12-08 enable third button on v0
2017-12-08 move compile-type flags from platformio.ini to config headers
2017-12-09 minor cleanup
2017-12-13 use a 6-pin ICSP connector
2017-12-13 add the sound circuit
2017-12-13 add TODOs
2017-12-13 improve the sound circuit
2017-12-13 complete the 2.0 schematic
2017-12-15 add volume control
2017-12-15 reshuffle the atmega pins
2017-12-16 get gid of 2 nested sheets
2017-12-17 minor schamatic changes
2017-12-17 start mapping components to footprints
2017-12-17 update lastPressedMs
2017-12-17 Fixes for brain and reset
2017-12-20 finish mapping components to footprints
2017-12-20 test point, 6th player socket
2017-12-20 place the RJ10 sockets on the PCB
2017-12-21 first attempt at laying out the 2.0 pcb
2017-12-21 add stitching vias, mounting holes
2017-12-21 silkscreen text
2017-12-21 move the LED a bit
2017-12-22 add a jumper for the volume regulator
2017-12-22 add a 128x64 LCD demo
2017-12-22 flip the LCD and re-route the board
2017-12-22 re-route everything again
2017-12-22 change socket and potentiometer footprints
2017-12-22 draw a bitmap in the 128x64 LCD demo
2017-12-22 pull LCD_CS down
2017-12-22 create a directory for gerber files
2017-12-23 remove DevMode class
2017-12-23 move LCD stuff into a separate header
2017-12-23 move the extra pins hack into a separate module
2017-12-23 disable the extra pins hack when not needed
2017-12-23 simplify the reset code a bit
2017-12-23 set resetStarted to false
2017-12-23 put screen size constants into lcd.h and use them everywhere
2017-12-23 use strncpy instead of strcpy
2017-12-23 show a message on startup
2017-12-24 make the schematic look nicer
2017-12-24 some more schematic improvements
2017-12-25 fix a resistor value
2017-12-25 move a couple of tracks
2017-12-25 add a missing resistor
2017-12-26 fix track clearance
2017-12-26 a few minor PCB changes
2017-12-26 reroute the differential pair
2017-12-28 replace the button footprints
2017-12-28 fix the buzzer footprint, move usb sockets
2017-12-28 update routing
2017-12-29 move a couple components
2017-12-29 start drawing a Kamaji XL schematic
2017-12-30 use a custom home_dir
2017-12-30 pull HWB down
2017-12-30 bump the PCB version
2018-01-02 add the tetris demo
2018-01-04 adjust the tetris demo for the new board
2018-01-04 update demos
2018-01-04 add config for v2 and an LCD wrapper
2018-01-04 update CircleCI config
2018-01-04 xpins for atmega32u4
2018-01-04 define the extra pins for v2
2018-01-04 don't define USE_XPINS_HACK in the config headers
2018-01-04 fix GraphicLcd
2018-01-04 add dummy load and signal led pins to the config
2018-01-04 use LCD in the paged mode to save memory
2018-01-04 move a couple tracks and vias
2018-01-04 try using software emulated SPI for the LCD
2018-01-04 Revert "try using software emulated SPI for the LCD"
    This reverts commit f480e49c37e6329675e11cf027eb54b90cdfbea2.
2018-01-05 set GraphicLcd parameters via template arguments
2018-01-05 use 2-page LCD mode, move font definition to lcd.h
2018-01-06 clean up lcd.h
2018-01-06 reverse the player socket order
2018-01-06 fix the test firmware
2018-01-06 update the CircleCI config
2018-01-06 fix the font width
2018-01-07 a bit of cleanup
2018-01-09 3d: fix OpenSCAD compilation errors
2018-01-22 enclosure v2 draft
2018-01-24 Move gaiki up
2018-01-29 enclosure tweaks
2018-01-30 Moar tweaks for enclosure v2
2018-02-12 edged top v2
2018-02-27 Rounded box
2018-02-27 Improved display
2018-03-04 Enable lamp in v2
2018-03-04 Export the schematic to PDF for convenience
2018-03-04 Disable RX/TX LEDs in the bootloader
2018-03-04 Add bootloader .HEX files
2018-03-04 Ich spreche Russisch
2018-03-04 Fix v0 build
2018-03-04 Pin library versions
2018-03-12 Minor fixes
2018-03-15 Brain and jeopardy
2018-03-15 Compilation error fix
2018-03-27 Reset in brain, multiple players in brain
2018-03-27 Bug fix
2018-03-28 3d: wider master buttons
2018-03-28 util to organize svoyak
2018-03-28 svoyak: stash
2018-04-09 cleanup, add v1 schematic in pdf
2018-04-09 start the v3 schematic
2018-04-09 most part of the v3 schematic
2018-04-11 finish the v3 schematic and map most of the footprints
2018-04-12 change screen and buttons footprints
2018-04-15 mostly finish the v3 layout
2018-04-15 v3 PCB: final touches
2018-04-15 add v3 schematic PDF
2019-02-02 start the v3 schematic from scratch
2019-02-03 finish v3 schematic
2019-02-03 v3: draw missing footprints, start layout
2019-02-03 v3: initial component placement
2019-02-03 v3: move components around
2019-02-05 v3: minor layout improvements
2019-03-02 add gerbers directory
2019-04-17 Brain fix
2019-04-28 Use src_build_flags instead of build_flags to fix a compilation issue
2019-05-01 v3.1 schematic
2019-05-15 Print v3.1 PCB
2019-09-08 add a capacitor to fix sound
2019-09-08 Print pcb v3.2
2019-09-08 Add v3 firmware config
2020-02-02 Fix build failure
2020-02-02 Set up Github Actions
2020-02-02 Remove CircleCI configuration
2020-02-02 Fix install commands in github actions configuration
2020-02-02 Add github actions badge to readme
2020-02-02 Fix deprecation warnings in platformio.ini
2022-10-08 Migrate v3 PCB to newer KiCAD
2022-10-08 Remove v0 firmware and clean up PlatformIO config
2022-10-09 Fix CI
2022-10-12 Button PCB: minor changes
2022-10-24 Generate gergers
2022-10-24 Tweak the button PCB
2022-11-19 Lay out Headless V1.0 board
2022-11-19 Headless: minor PCB tweaks
2022-11-20 Add gerbers
2022-12-04 Button PCB v1.1
2022-12-05 Headless: add STEP model
2022-12-08 Headless PCB v1.2
2022-12-08 Tweak a trace, cleanup
2022-12-09 Add MIDI device firmware (for Headless)
2022-12-09 Add WebMIDI demo
2022-12-10 Extend WebMIDI demo
2022-12-27 button pcb: replace the switch footprint
2022-12-27 button pcb: update silkscreen
2023-01-04 Change MIDI channels
2023-01-12 Add headless v1 enclosure files
2023-01-14 Minor tweaks to button PCB silkscreen
2023-01-14 Add gerbers archive
2023-01-14 Add Headless PCB gerbers
2023-02-13 Add Classic schematic
2023-02-18 Classic: Finish first pass of routing
2023-02-18 Final PCB layout tweaks
2023-03-04 Minor tweaks to the classic PCB
2023-03-11 Update gitignore
2023-03-11 Classic: PCB revision 1.1
2023-05-06 Add shell STLs and CAD files for Classic and button
2024-02-20 Improvements: - better undo handling for jeopardy - persistent options for brain
2024-02-25 disable some u8g2 features in an attempt to reduce binary size
2024-02-25 Revert "disable some u8g2 features in an attempt to reduce binary size"
    This reverts commit 011d86ad2b56e56c69b2c322de67aa22986bfc65.
2024-10-18 Fix for brain with no falsestarts
2024-10-21 Fix for fix for brain with no falsestarts
2024-10-21 src/lcd.h: use u8g2_font_6x13B_tr for non-RUSSIAN builds
    This is needed to reduce the firmware size
2024-10-21 v2: temporarily disable Russian in v2
2025-12-30 Update KiCAD projects, add Classic V1 schematic PDF
2025-12-30 Update the test firmware
2025-12-30 Update Headless KiCAD project
2026-03-09 Fix for accidental reset

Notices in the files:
pcb/2.0/kamaji.sch:
© Ilya Strukov 2017
